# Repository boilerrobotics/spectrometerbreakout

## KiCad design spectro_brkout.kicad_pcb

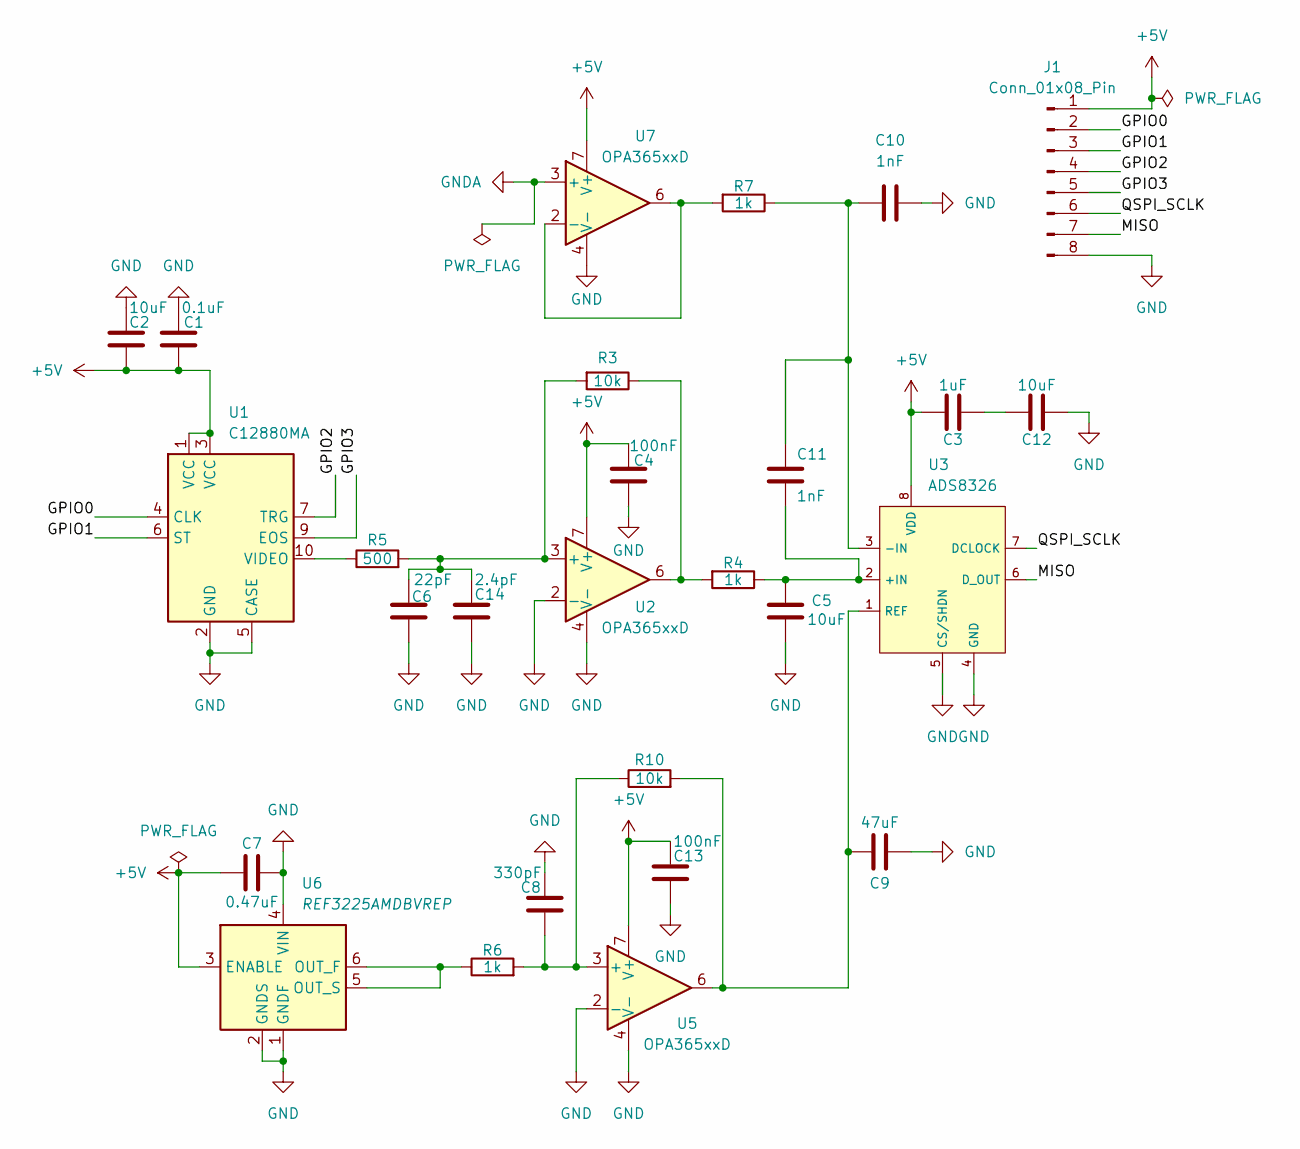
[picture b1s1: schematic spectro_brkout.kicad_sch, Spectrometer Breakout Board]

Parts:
C1: 0.1uF; C_0603_1608Metric_Pad1.08x0.95mm_HandSolder
C2, C5, C12: 10uF; C_0805_2012Metric_Pad1.18x1.45mm_HandSolder
C3: 1uF; C_0603_1608Metric_Pad1.08x0.95mm_HandSolder
C4, C13: 100nF; C_0603_1608Metric_Pad1.08x0.95mm_HandSolder
C6: 22pF; R_0603_1608Metric_Pad0.98x0.95mm_HandSolder
C7: 0.47uF; C_0603_1608Metric_Pad1.08x0.95mm_HandSolder
C8: 330pF; C_0603_1608Metric_Pad1.08x0.95mm_HandSolder
C9: 47uF; C_0805_2012Metric_Pad1.18x1.45mm_HandSolder
C10, C11: 1nF; C_0603_1608Metric_Pad1.08x0.95mm_HandSolder
C14: 2.4pF; R_0603_1608Metric_Pad0.98x0.95mm_HandSolder
J1: Conn_01x08_Pin; PinHeader_1x08_P2.54mm_Vertical
R3, R10: 10k; R_0805_2012Metric_Pad1.20x1.40mm_HandSolder
R4, R6, R7: 1k; R_0805_2012Metric_Pad1.20x1.40mm_HandSolder
R5: 500; R_0805_2012Metric_Pad1.20x1.40mm_HandSolder
U1: C12880MA; Hamamatsu_C12880
U2, U5, U7: OPA365xxD; SOIC-8_3.9x4.9mm_P1.27mm
U3: ADS8326; HVSSOP-8-1EP_3x3mm_P0.65mm_EP1.57x1.89mm_ThermalVias
U6: REF3225AMDBVREP; SOT-23-6

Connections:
+5V: C1.1, C2.1, C3.2, C4.1, C7.1, C13.1, J1.1, U1.1 (VCC), U1.3 (VCC), U2.7 (V+), U3.8 (VDD), U5.7 (V+), U6.3 (ENABLE), U7.7 (V+)
/GPIO0: J1.2, U1.4 (CLK)
/GPIO1: J1.3, U1.6 (ST)
/GPIO2: J1.4, U1.7 (TRG)
/GPIO3: J1.5, U1.9 (EOS)
/MISO: J1.7, U3.6 (D_OUT)
/QSPI_SCLK: J1.6, U3.7 (DCLOCK)
GND: C1.2, C2.2, C4.2, C5.2, C6.2, C7.2, C8.1, C9.1, C10.2, C12.1, C13.2, C14.2, J1.8, U1.2 (GND), U1.5 (CASE), U2.2 (-), U2.4 (V-), U3.4 (GND), U3.5 (CS/SHDN), U5.2 (-), U5.4 (V-), U6.1 (GNDF), U6.2 (GNDS), U6.4 (VIN), U7.4 (V-)
GNDA: U7.3 (+)
unnamed: C3.1, C12.2
unnamed: R3.1, R4.2, U2.6
unnamed: R5.1, U1.10 (VIDEO)
unnamed: C6.1, C14.1, R3.2, R5.2, U2.3 (+)
unnamed: C5.1, C11.2, R4.1, U3.2 (+IN)
unnamed: C10.1, C11.1, R7.1, U3.3 (-IN)
unnamed: C9.2, R10.2, U3.1 (REF), U5.6
unnamed: C8.2, R6.2, R10.1, U5.3 (+)
unnamed: R6.1, U6.5 (OUT_S), U6.6 (OUT_F)
unnamed: R7.2, U7.2 (-), U7.6

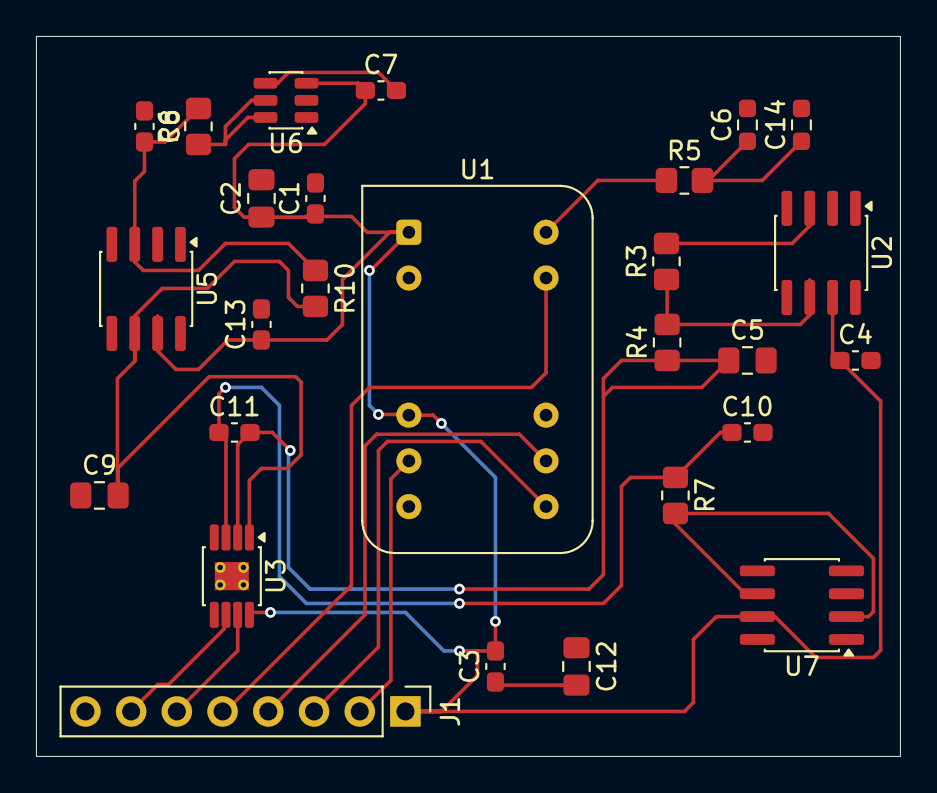
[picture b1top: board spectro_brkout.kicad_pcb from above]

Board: 2 copper layers, 48.0 x 40.0 mm, 27 parts (0 on the bottom side), 18 nets.
